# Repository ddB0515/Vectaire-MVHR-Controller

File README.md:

# Vectaire MVHR controller

<div align="center">
  
  <br><br>
  
  &nbsp;&nbsp;
  
</div>

ESP32 firmware that **replaces the original LCD control panel** of a Vectaire MVHR (heat-recovery ventilation) unit.
It is tested on the **Vectaire Midi** and may also work with the **Maxi**, which uses the same kind of panel (see
[MVHR units](#mvhr-units)).
The controller talks to the unit over its 12 V one-wire bus. It shows everything on its own touch screen, or works
without a screen, and you can also use it from a phone or a computer:

- **Local touch screen** (optional): home screen with temperatures, humidity, fan speed and alarms, plus menus for
  every setting the original panel had.
- **Web page** on your home network: live state, controls, settings, maintenance and diagnostics.
- **Home Assistant** through MQTT discovery. All sensors and controls appear by themselves.
- **Firmware updates over Wi-Fi**, with automatic rollback if a new version fails.

> The controller is the **only master** on the bus: it replaces the original panel, it doesn't sit next to it.
> Disconnect the original panel before you connect the controller.

---

## Contents

1. [Two variants](#two-variants)
2. [Supported hardware](#supported-hardware)
3. [Wiring to the MVHR](#wiring-to-the-mvhr)
4. [First start and Wi-Fi setup](#first-start-and-wi-fi-setup)
5. [Using the touch screen](#using-the-touch-screen)
6. [Web page](#web-page)
7. [Home Assistant](#home-assistant)
8. [Network time](#network-time)
9. [Fan speed settings](#fan-speed-settings)
10. [Not built yet](#not-built-yet)
11. [Device password](#device-password)
12. [Button and status LED](#button-and-status-led)
13. [Troubleshooting](#troubleshooting)
14. [Project layout](#project-layout)
15. [Building, flashing and updating: `idf.sh` and `ota.sh`](#building-flashing-and-updating-idfsh-and-otash)

---

## Two variants

The same code builds two variants:

| | **Display** | **Headless** |
|---|---|---|
| Board | NiceMCU C5E-DEV 2.8IPS (ESP32-C5, 2.8" touch screen) | Any ESP32, ESP32-C3, -S3, -C5 or -C6 board, 4 MB flash or more |
| Operated from | Touch screen, web page, Home Assistant | Web page, Home Assistant |
| Status shown on | Screen | A status LED (optional) |
| Wi-Fi | Optional ("Display only" mode works without it) | Required |
| Wi-Fi setup | Hotspot with a password and a QR code on the screen | Open hotspot that closes after 15 minutes |

Both variants have the same bus driver, web pages, Home Assistant integration and OTA updates.
An update can't install one variant's firmware on the other.

## Supported hardware

### Display variant

**NiceMCU C5E-DEV 2.8IPS**:
- ESP32-C5 (rev 1.2), 16 MB flash, 8 MB PSRAM,
- ST7789 320×240 IPS screen,
- CST816D touch controller.

The board's schematic, display spec and vendor demo are in [`docs/board/`](docs/board/).

### Headless variant

| Chip | Wi-Fi | Notes |
|---|---|---|
| ESP32 (classic, e.g. ESP32-D0WDQ6 DevKit) | 2.4 GHz | Wi-Fi setup and web page tested; not yet on a real bus |
| ESP32-S3 | 2.4 GHz | builds, not yet tested on hardware |
| ESP32-C3 | 2.4 GHz | builds, not yet tested on hardware |
| ESP32-C6 | 2.4 GHz | builds, not yet tested on hardware |
| ESP32-C5 | 2.4 + 5 GHz | builds, not yet tested on hardware |

PSRAM is not needed. The default pins for each chip are in [Wiring](#default-pins), and
[`docs/HEADLESS.md`](docs/HEADLESS.md) has more on the headless variant.

### MVHR units

| Unit | Status |
|---|---|
| **Vectaire Midi** | Tested: the controller runs in place of the original LCD panel |
| **Vectaire Maxi** | Not tested. It may work, as it uses the same LCD panel on the same one-wire bus, but check it carefully first |

The controller works with Vectaire units that use the original LCD panel on the one-wire bus (1200 baud). Units with
config block version 1.3 (49 bytes) and 2.0 (67 bytes) are recognised.

If you try it on a Maxi (or another Vectaire unit), keep the original panel so you can put it back, start with
**Diagnostics** to confirm the unit answers, and please report what works.

### Front panel (3D print)

[`midi-panel-3d-model/`](midi-panel-3d-model/) has a 3D-printable front panel for the display variant, made for the
**Vectaire Midi**:

| File | What it is |
|---|---|
| `Front Panel.stl` / `Front Panel.step` | The front panel that holds the display board |
| `PSU Plate.stl` / `PSU Plate.step` | The PSU plate |
| `Vectaire MVHR Screen Panel.f3d` | The Fusion 360 source, for changes |

Print the `.stl` files; the `.step` files are for other CAD programs. The photo at the top of this README shows the
panel fitted to a Midi.

You will also need **M3 threaded inserts** (heat-set into the printed parts):

| Part | Inserts |
|---|---|
| Front panel, for the screen | 4 × M3 × 4 mm |
| PSU plate | 4 × M3 × 5.5 mm |

## Wiring to the MVHR

The bus has a single signal wire that idles at **+12 V**, with the pull-up inside the unit. The controller needs two
GPIOs: one to **send** (TX), which pulls the bus low through an NPN transistor, and one to **receive** (RX), which reads
the bus through a voltage divider.

```
                     MVHR unit
              +12 V ───┐ (pull-up inside the unit)
                       │
   BUS ────────────────┴──────────┬───────────────────┐
                                  │                   │
                               C  │                 [15k]
   ESP TX ────[10k]────┬── B  NPN │ (e.g. 2N2222,     │
                       │       E  │  BC547)           ├──── ESP RX   (≈2.9 V at 12 V)
                     [100k]       │                   │
                       │          │                 [4.7k]
   GND ────────────────┴──────────┴───────────────────┴──── MVHR GND
```

- **TX:** the firmware inverts TX, so the transistor is off while the bus is idle. The 100k resistor from base to GND
  keeps the bus free while the ESP32 starts up.
- **RX:** the 15k/4.7k divider brings 12 V down to about 2.9 V. Don't use a divider that gives more than 3.3 V.
- **GND** of the controller and the unit must be connected.
- **Power:** use a proper supply. Some USB power banks switch off at low load, which restarts the controller.

Verified hardware adopter slightly modified is in `hardware` folder https://github.com/ddB0515/VectaireESP32/tree/main/hardware

### Default pins

| Board / chip | Bus TX | Bus RX | Button | Status LED |
|---|---|---|---|---|
| NiceMCU C5 (display) | IO2 (4-pin "I2C" connector, pin 3) | IO3 (pin 2) | GPIO28 | – |
| ESP32 | GPIO25 | GPIO26 | GPIO0 (BOOT) | GPIO2, single LED |
| ESP32-S3 | GPIO17 | GPIO18 | GPIO0 (BOOT) | GPIO48, WS2812 |
| ESP32-C3 | GPIO4 | GPIO5 | GPIO9 (BOOT) | GPIO8, WS2812 |
| ESP32-C6 | GPIO2 | GPIO3 | GPIO9 (BOOT) | GPIO8, WS2812 |
| ESP32-C5 (headless) | GPIO2 | GPIO3 | GPIO28 (BOOT) | GPIO27, WS2812 |

All pins can be changed. See [Changing pins and options](#changing-pins-and-options).

**Checking the wiring without a unit attached:** open the web page's **Diagnostics** and press **Run wiring test**.
It pulls the bus low for about 20 ms and checks that RX sees it.

## First start and Wi-Fi setup

### Display variant

On first start the screen offers two choices:

- **Wi-Fi & Home Assistant:** the controller opens a setup hotspot and shows a QR code.
  1. Scan the QR code with your phone to join the hotspot.
  2. The setup page opens by itself. Scan the second QR code if it doesn't.
  3. Pick your network, enter its password and, if you like, your MQTT broker.
- **Display only:** no Wi-Fi at all. Everything works from the touch screen.

### Headless variant

1. Power the controller up. With no Wi-Fi saved, it opens the **open hotspot** `Vectaire-XXXX`, and the LED blinks
   blue.
2. Join it with a phone. The setup page opens by itself, or go to `http://192.168.4.1/`.
3. **Write down the device password** shown at the top of the page.
4. Choose your Wi-Fi network, optionally enter your MQTT broker, and press **Connect**.

The hotspot closes after 15 minutes with nobody joined. Because it has no password, anyone nearby could join it while
it is up, so keep the setup short.

### After setup

The controller restarts and joins your network. From then on it is reachable at **`http://vectaire-xxxx.local/`**
(the name is on the setup page, and on the screen under Menu › Device). Use its IP address if your phone or computer
doesn't resolve `.local` names.

## Using the touch screen

**Home screen** shows:
- a house with the **airflow mode** under the roof (heat recovery in orange, bypass in blue, intake motor off in
  green, each with its icon) and the **inside temperature and humidity** along the bottom ("Low" below 35 %, "High"
  above 99 %, as on the original panel),
- the **intake and exhaust fan** percentages above the roof (intake left, exhaust right),
- the **outdoor temperature** on the right, with the current function below it when there is one (holiday, night
  mode …; "Boost active" during a boost),
- fan speed (1–3), with − and + buttons, and the bypass button,
- the time and date,
- a Wi-Fi icon (only while connected) and the Home Assistant logo (only while connected),
- an alarm banner when there is an alarm.

**Menu**:

| Item | What it does |
|---|---|
| Holiday | Off (normal ventilation) or On (reduced ventilation while away) |
| Night | Night mode (no boost during quiet hours): on/off, start and end time |
| Humidity | Humidity setpoint for automatic boost |
| Timers | Boost delay and overrun |
| Bypass | Summer bypass: auto, or forced on/off |
| Clock | Sets the unit's time and date by hand; **Network time** (see [Network time](#network-time)) |
| Filter | Filter saturation, hours of service, power outages; reset the filter counter after a filter change |
| Device | Wi-Fi, Home Assistant, dark theme, **dim after**, **dim level** (1, 5, 10, 25 or 50 %), **screen off after**, [**fan speeds**](#fan-speed-settings), **outdoor temp offset** (−10.0 to +10.0 °C in 0.1 steps), firmware version (tap it to see the device password) |

**Alarms** pop up by themselves. A **fire alarm** takes over the whole screen.

**Sleep:** the screen dims, then switches off when nobody touches it (both times and the dim level can be set under
Device). Tap to wake it: that first tap only wakes the screen and doesn't press anything. After 60 s without a touch it also goes back
to the home screen.

**Dark theme:** Menu › Device › Dark theme. It is saved and applied straight away.

## Web page

`http://vectaire-xxxx.local/` works on both variants and uses the phone's or computer's light or dark mode.

| Section | What's there |
|---|---|
| **Overview** | The same picture as the controller's home screen: airflow mode (with icon and colour), inside temperature and humidity, intake and exhaust fan %, outdoor temperature, and the current function |
| **Ventilation** | Fan speed, boost state (off / delay / on / overrun), bypass (with what it does now), holiday mode on/off |
| **Settings** | Humidity setpoint, boost delay, overrun, night mode, outdoor temperature offset |
| **Fan speed settings** | The installer fan percentages per speed. Shown only once the unit's settings have been read; editable when unlocked, see [Fan speed settings](#fan-speed-settings) |
| **Maintenance** | Filter saturation, reset filter counter, hours of service, the unit's clock (**Set unit clock to this device's time**, and [network time](#network-time)) |
| **Device** | Firmware, unit firmware, Wi-Fi, Home Assistant status, uptime; **Change Wi-Fi network** (scan, pick, password). The new network is tried first and kept only if it connects within 45 s, otherwise the controller goes back to the old one; **Change device password** (see [Device password](#device-password)) |
| **Changes** (at the bottom) | Unlock with the [device password](#device-password) to make changes; the password stays only in that browser tab |

Viewing needs no password; making changes does.

The links at the bottom open two more pages:
- **Home Assistant settings** (`/ha`): MQTT broker, user, password, the device name and how often readings are sent ("Update every", 5–3600 s, default 30; changes go out at once). Needs the device password; unlocking on the home page unlocks it too (same browser tab).
- **Diagnostics** (`/diag`): read-only, no password. Shows:
  - bus health and counters,
  - the last bus exchanges,
  - the wiring test,
  - the **unit's clock** as raw values (12/24 h, date format, time zone number, the UTC offset byte whose top bit may be the unit's own daylight saving flag),
  - the **outdoor temperature** three ways: as the unit reports it, the offset, and the value shown,
  - memory, Wi-Fi and the reason for the last restart,
  - a stored crash report, if there is one,
  - the full bus trace since start-up.

## Home Assistant

The controller uses **MQTT discovery**: once a broker is set, the device appears in Home Assistant with no YAML.
You need an MQTT broker (for example the Mosquitto add-on) and the MQTT integration.

1. Enter the broker during Wi-Fi setup, or later at `http://vectaire-xxxx.local/ha`.
2. Home Assistant shows a new device named after the controller (default "Vectaire MVHR").

| Type | Entities |
|---|---|
| Sensors | Inside/outside temperature, indoor humidity, intake/exhaust fan (%), mode (heat recovery / bypass / intake motor off), boost (off / delay / on / overrun), filter saturation, function, alarm, hours of service, power outages, Wi-Fi signal |
| Controls | Fan speed (1/2/3), bypass, holiday mode, night mode, humidity setpoint, boost delay, overrun |
| Binary sensors | Problem, fire alarm, frost protection |
| Button | Reset filter counter |

The **outdoor temperature** sent to Home Assistant includes the **outdoor temperature offset** (Menu › Device, or the
Settings card on the web page): a correction of −10.0 to +10.0 °C in 0.1 steps for a sensor that reads a little high or low.
The same corrected value is shown on the screen and the web page; the Diagnostics page lists the unit's own reading,
the offset and the shown value. The offset changes only what is displayed and reported, not what the unit itself uses.
A new offset reaches Home Assistant with the next regular update (the "Update every" time).

The entities show **unavailable** when the controller is offline, and also when the unit doesn't respond on the bus.

The **alarm** sensor reads "No alarm" when all is well (Home Assistant would show "Unknown" for the text "None").

MQTT topics, for the curious:
- discovery: `homeassistant/<component>/<id>/<obj>/config`
- state: `vectaire/<id>/state` (retained JSON)
- commands: `vectaire/<id>/<obj>/set`
- availability: `vectaire/<id>/status` and `vectaire/<id>/unit`

## Network time

The controller can set the unit's clock from the internet. It needs Wi-Fi, so it is **off by default**. The clock can
also always be set by hand: on the screen (Menu › Clock › Set time / Set date), or on the web page with **Set unit
clock to this device's time**, which uses the time of the phone or computer you are on.

| Setting | Meaning |
|---|---|
| **Network time** | On or off (Menu › Clock › Network time, or the web page's Maintenance card) |
| **Time zone** | Pick a city or region from the list, for example London, Berlin, New York / Toronto or Tokyo / Seoul. Each entry carries its standard (winter) time offset from UTC and its summer time rule. On the screen: Menu › Clock › Network time › Time zone (a scrolling list). On the web page: the Time zone menu, which shows entries as `(UTC+01:00) Berlin (summer time)` |

How it works:
- About a minute after start-up, and then **once a day**, the controller asks `pool.ntp.org` for the time.
- From that and the time zone it works out what the unit's clock should show, including the hour. The zone's summer
  time rule (last Sunday of March and October for the UK and Europe, second Sunday of March and first Sunday of
  November for the US and Canada) is used only to know whether summer time is on at that moment; the controller never
  moves the clock by itself on the changeover dates, so with network time off the clock only changes when you set it.
- If the clock is **more than 2 minutes out**, it is set to the right time (the unit has no seconds). If it is within
  2 minutes nothing is changed.
- With no Wi-Fi, no answer from the server or an unreadable clock, it tries again after about 10 minutes (5 minutes if
  the unit's clock could not be read). **Check now** (screen and web page) runs a check at once.
- The result of the last check is shown under the setting, for example "Last check 3 h ago: the clock was 5 min fast
  and was corrected."

The list holds regions whose summer time follows the European or the North American rule, plus regions with no summer
time (UTC, Reykjavik, Tokyo / Seoul, Dubai and others). Regions with southern-hemisphere summer time, such as Sydney
or Auckland, are not in the list. Without Wi-Fi the clock keeps running on the unit's own clock and is changed by hand
when needed.

To add a region, add a line to `components/mvhr_model/timezones.c`: the web page, the screen and the web preview all
read that one table.

> The night-mode quiet hours use the unit's clock, so a wrong time zone or rule moves them.

## Fan speed settings

The unit stores how hard each fan runs at speed 1, 2 and 3 (intake and exhaust separately, as set when the unit was
commissioned), plus a frost stall speed and a holiday reduction. The original panel hides these behind an installer
PIN. This firmware can show them, and change the six intake and exhaust values.

| Where | How |
|---|---|
| **Screen** | Menu › Device › **Fan speeds**. Tap a value, change it in whole percent (10–100), tap Set, read the warning, then Apply |
| **Web page** | **Fan speed settings** card. Unlock, edit the boxes (values show with a % sign; type just the number), press Save |

Both show a warning first. It says you are changing the fan speed balance and lists the **original values** so you can
write them down and put them back. The values are 10.0–100.0 % of full fan speed; the firmware refuses anything outside
that. Frost stall speed and holiday reduction are shown but cannot be changed.

How a change reaches the unit: the controller reads the unit's installer config block (49 bytes) again, changes only
the fan bytes you edited, writes the whole block back (command `0x10`), and reads it again to check. The log says
"now reports the new values" or "does NOT report the new values". All other installer settings are sent back exactly as
the unit gave them.

> **Be careful.** These settings change how much air each speed moves and the balance between intake and exhaust.
> Note the original values before changing anything, and change one value at a time while you check the unit.
> Changing the fan speeds has not yet been confirmed on every unit, so try it on one value first.

## Not built yet

- **Daylight saving without a network:** the controller does not change the clock by itself on the changeover dates.
  Network time (or setting it by hand) does that.
- **Southern-hemisphere summer time:** the time zone list has no Sydney, Auckland and similar regions, because only the
  European and North American summer time rules are built in.
- **More installer settings:** only the six intake and exhaust fan percentages can be changed. Frost stall speed and
  holiday reduction are shown but read-only, and the other installer settings (frost and bypass thresholds, heater
  threshold, handing) are not shown.
- **Fan speed write:** changing the fan speeds has not been confirmed on every unit.

## Device password

Each controller generates its own **device password** on its first start and keeps it in its flash. Updates don't
change it, but you can replace it with your own from the web page (see below). It protects:

- firmware updates over Wi-Fi,
- changes from the web page,
- the Home Assistant settings page,
- remote restart.

Where to find it:
- **Display:** Menu › Device, then tap the **Firmware** row.
- **Headless:** at the top of the setup page. Press the button for 1–4 s to open the setup hotspot again and read it.

The password is never stored on your computer by the tools in this project.

**Changing it:** on the home page, unlock with the current password, then **Device › Change device password**. The
first time, the current password is the generated one. Enter it again, then the new one twice: 8–32 characters,
letters, digits and symbols, no spaces. From then on the new password is needed for everything above (including
`tools/ota.sh`), and the screen (or the setup page, headless) shows the new one. The API is `POST /api/password` with
the current password in `X-OTA-Password` and `{"new":"..."}` as the body. A factory install over USB erases it and a
new one is generated.

## Button and status LED

| Button | Display | Headless |
|---|---|---|
| 1–4 s | – | Opens the setup hotspot (change Wi-Fi, see the device password); nothing is forgotten |
| Hold 5 s | Forgets Wi-Fi and restarts into the first-start choice | Forgets Wi-Fi and restarts into setup |

MQTT settings are kept in both cases.

**Status LED** (headless only; a WS2812 shows colours, a single LED shows only the blink pattern):

| State | Colour | Pattern |
|---|---|---|
| Fire alarm | red | fast flicker |
| Setup hotspot open | blue | blinks once a second |
| Unit not responding | red | double flash every 2 s |
| Connecting to Wi-Fi | yellow | short flash every 2 s |
| Other alarm (e.g. clean filters) | orange | on, short gap every 2 s |
| All fine | green | on |

## Troubleshooting

| Symptom | What to check |
|---|---|
| "Unit not responding" | Diagnostics › **Run wiring test**. **No bus voltage on RX:** check the BUS wire, the divider and GND. **TX doesn't pull the bus low:** check the transistor, the base resistor and the TX pin. |
| Unit responds only sometimes | Diagnostics › Bus: timeouts, CRC errors and bytes heard while idle. Make sure the original panel is disconnected. |
| Controller restarts by itself | Diagnostics › System › **Last restart**. "Power on" means the supply dropped (power banks do this); "Crash" comes with a stored crash report. |
| Can't reach `vectaire-xxxx.local` | On Linux, install `avahi-daemon` and `libnss-mdns`; under WSL, `ota.sh` asks Windows by itself. Or use the IP address (shown on the screen, in your router, or on the setup page after connecting). |
| Wrong Wi-Fi, or moved house | Still reachable: Device › Change Wi-Fi network on the web page. Otherwise hold the button for 5 s (or, headless, press it for 1–4 s) and run the setup again. Without Wi-Fi the controller restarts after 15 minutes offline, trying again. |
| Update didn't take | The new firmware rolls back by itself if it crashes or doesn't reach Wi-Fi within 5 minutes. Check the version under Device. |

## Project layout

| Path | What it is |
|---|---|
| `main/` | Start-up, button, Kconfig options (pins, LED, simulator) |
| `components/vectaire_bus` | Bus framing, CRC and UART transactions |
| `components/mvhr_model` | Polls the unit, decodes its data, sends commands; built-in **unit simulator** for development |
| `components/net` | Wi-Fi, setup hotspot and page, mDNS, OTA updates |
| `components/web` | Home page, diagnostics and JSON API |
| `components/ha` | Home Assistant (MQTT discovery) |
| `components/autoclock` | Daily network time for the unit's clock (summer time rules in `mvhr_model/dst.c`, the time zone list in `mvhr_model/timezones.c`, the decision logic in `mvhr_model/timesync.c`) |
| `components/settings` | Saved settings (NVS) |
| `components/status_led` | Headless status LED |
| `components/board`, `components/ui` | Display variant only: screen, touch, LVGL screens |
| `test/host/` | Unit tests for the bus codec, decoder and simulator; these run on a PC |
| `tools/` | `idf.sh`, `ota.sh`, `gen_icons.py` (screen icons), `web_preview.py` (web page preview) |
| `docs/` | [`HEADLESS.md`](docs/HEADLESS.md); `home_preview.html` (mock of the home screen); `board/`: vendor schematic, display spec and demo sketch |
| `midi-panel-3d-model/` | 3D-printable front panel and power supply plate for the Vectaire Midi (STL, STEP, Fusion 360) |
| `photos/` | Photos used in this README |

**Host tests** run on a PC and don't need ESP-IDF:

```bash
gcc -Icomponents/vectaire_bus/include -Icomponents/mvhr_model/include -Icomponents/mvhr_model -Itest/host/stub \
    components/vectaire_bus/vbus_codec.c components/mvhr_model/mvhr_decode.c test/host/test_decode.c \
    -o /tmp/test_decode && /tmp/test_decode
gcc -Icomponents/vectaire_bus/include -Icomponents/mvhr_model/include -Icomponents/mvhr_model -Itest/host/stub \
    components/vectaire_bus/vbus_codec.c components/mvhr_model/mvhr_decode.c components/mvhr_model/mvhr_sim.c \
    test/host/test_sim.c -o /tmp/test_sim && /tmp/test_sim
gcc -Icomponents/mvhr_model/include -Icomponents/mvhr_model -Itest/host/stub components/mvhr_model/dst.c \n    test/host/test_dst.c -o /tmp/test_dst && /tmp/test_dst
gcc -Icomponents/mvhr_model/include -Icomponents/mvhr_model -Itest/host/stub components/mvhr_model/dst.c     components/mvhr_model/timesync.c test/host/test_timesync.c -o /tmp/test_timesync && /tmp/test_timesync
```

**Unit simulator:** to develop without an MVHR, enable "Always use the built-in unit simulator" in menuconfig
(menu "Vectaire"). The bus UART is then not used at all. The simulated unit accepts the fan-speed config write too.

**Previewing the web page without building:** `python tools/web_preview.py [port]` serves
`components/web/www/home.html` straight from disk with made-up data, so you can edit the page and refresh the browser.
A "Preview controls" panel (bottom right) changes the data: function, airflow mode, temperatures, fan %, alarms,
Home Assistant and Wi-Fi status and so on. Any password unlocks the page. If the port is busy, pick another one;
old preview windows keep their port.

**Previewing the home screen:** open `docs/home_preview.html` in a browser. It is a mock of the controller's home
screen with switches for the Wi-Fi and Home Assistant icons and other states; it is not generated from the firmware, so
update it together with `components/ui/ui_home.c`.

**Icons:** the screen's icons are generated from SVG paths in `tools/gen_icons.py` into `components/ui/icons.c`
and `icons.h`. After changing icons run `python3 tools/gen_icons.py` (needs `librsvg2-bin` and `imagemagick`).

---

## Building, flashing and updating: `idf.sh` and `ota.sh`

### Setting up

The build tools are bash scripts and run on **Linux** or on **Windows 11 through WSL 2** (Windows Subsystem for Linux).
Both need **ESP-IDF v6.1**, installed with Espressif's installer (EIM) so that
`~/.espressif/tools/activate_idf_v6.1.sh` exists. `tools/idf.sh` uses that file; you never need to activate ESP-IDF
yourself. v5.5.4 still works (`tools/idf.sh --idf 5.5.4 build`, or `export VECTAIRE_IDF=5.5.4`).

The first build downloads the managed components (LVGL, mDNS, LED strip driver, and under v6 also MQTT and cJSON).

#### Linux (Ubuntu / Debian)

```bash
# build prerequisites, curl and python3 for ota.sh
sudo apt update
sudo apt install -y git wget flex bison gperf python3 python3-pip python3-venv cmake ninja-build ccache \
    libffi-dev libssl-dev dfu-util libusb-1.0-0 curl

# ESP-IDF Installation Manager (EIM) from Espressif's apt repository, then ESP-IDF v6.1
echo "deb [trusted=yes] https://dl.espressif.com/dl/eim/apt/ stable main" | sudo tee /etc/apt/sources.list.d/espressif.list
sudo apt update && sudo apt install -y eim
eim install -i v6.1

# access to USB serial ports (log out and back in afterwards)
sudo usermod -aG dialout $USER

# optional: open controllers by name (vectaire-xxxx.local)
sudo apt install -y avahi-daemon libnss-mdns
```

Then clone the project and build: `tools/idf.sh build`.

#### Windows 11 (WSL 2)

Everything runs inside an Ubuntu installation in WSL 2. The web pages open in your normal Windows browser.

1. **Install WSL with Ubuntu.** In PowerShell as administrator, run `wsl --install -d Ubuntu-24.04`, restart, and
   create your Linux user when Ubuntu starts.
2. **In the Ubuntu terminal,** run the same commands as for [Linux](#linux-ubuntu--debian) above. Skip avahi; Windows
   resolves `.local` names for `ota.sh`, see point 5.
3. **Clone the project inside WSL**, e.g. `cd ~ && git clone <repo-url>`. Not under `/mnt/c/...`: building there
   is many times slower. The repository's `.gitattributes` keeps the scripts' LF line endings even in a Windows
   checkout. A CRLF script fails with `bash\r: No such file or directory`; fix one with `git add --renormalize .`
   or a fresh clone.
4. **USB for flashing.** WSL doesn't see USB devices until Windows hands them over with
   [usbipd-win](https://github.com/dorssel/usbipd-win). In PowerShell:

   ```powershell
   winget install usbipd                     # once
   usbipd list                               # find the board: "USB-SERIAL CH340", "CP210x" or "USB JTAG/serial debug unit"
   usbipd bind --busid 1-4                   # once per board, as administrator (use your BUSID)
   usbipd attach --wsl --busid 1-4           # every time the board is plugged in
   ```

   In Ubuntu it then appears as `/dev/ttyUSB0` (CH340, CP210x) or `/dev/ttyACM0` (the chip's own USB). Check with
   `ls /dev/ttyUSB* /dev/ttyACM*`. If the port is missing, `tools/idf.sh` prints these steps. Opening the port
   resets some boards, the NiceMCU C5 among them; it may then drop off WSL, so run `usbipd attach` again.
5. **Over-the-air updates need no setup.** WSL 2 usually can't resolve `.local` names itself, so `tools/ota.sh` asks
   Windows for the address and prints it (`vectaire-xxxx.local is 192.168.1.50`). You can always pass the IP
   instead. If you use the controllers' names in other commands too (e.g. `curl`), turn on WSL's mirrored
   networking: add `[wsl2]` and `networkingMode=mirrored` to `%UserProfile%\.wslconfig`, then run `wsl --shutdown`.
6. **VS Code:** install the **WSL** extension, open the project folder from WSL (`code .` in the Ubuntu terminal), and
   install the ESP-IDF extension inside WSL. Point it at the same v6.1 (`~/.espressif/v6.1/esp-idf`); a build
   folder configured by another version is started over by `tools/idf.sh`.

After that, every command below is the same on Windows (in the Ubuntu terminal) and on Linux.

### `tools/idf.sh`: build and flash

`tools/idf.sh` runs ESP-IDF's `idf.py` with the pinned ESP-IDF version. You don't need an activated ESP-IDF shell, and
it works from scripts. Everything after the variant option goes straight to `idf.py`.

Each build folder remembers which ESP-IDF version configured it. If you switch versions (or VS Code's ESP-IDF
extension used another one in the same folder), `idf.sh` starts that folder over and keeps its `sdkconfig`.

```
tools/idf.sh [--idf <version>] [--headless <target>] <idf.py arguments>
```

| Variant | Build folder | Settings file | Firmware image |
|---|---|---|---|
| Display (default) | `build/` | `sdkconfig` | `build/vectaire_c5.bin` |
| `--headless esp32` | `build-headless-esp32/` | `build-headless-esp32/sdkconfig` | `build-headless-esp32/vectaire_headless.bin` |
| `--headless esp32c3` / `esp32s3` / `esp32c5` / `esp32c6` | `build-headless-<target>/` | inside that folder | `…/vectaire_headless.bin` |

The variants never share a build folder or settings file, so you can build all of them side by side.

**Display variant**, the NiceMCU C5 board:

```bash
tools/idf.sh build                              # build
tools/idf.sh -p /dev/ttyUSB0 flash              # flash over USB (first time, or to recover)
tools/idf.sh -p /dev/ttyUSB0 flash monitor      # flash and watch the log (Ctrl+] to quit)
tools/idf.sh menuconfig                         # settings, menu "Vectaire"
```

The board's USB serial chip is a CH340 (`/dev/ttyUSB0`, 115200 baud). Opening the serial port power-cycles this
board.

**Headless variant**, for example a classic ESP32:

```bash
tools/idf.sh --headless esp32 build
tools/idf.sh --headless esp32 -p /dev/ttyUSB0 flash
tools/idf.sh --headless esp32 -p /dev/ttyUSB0 monitor
tools/idf.sh --headless esp32 menuconfig
```

#### Changing pins and options

Run `menuconfig` for the variant and chip, open the **Vectaire** menu, save, then build again:

| Option | Meaning |
|---|---|
| MVHR bus TX GPIO | Output to the NPN base resistor |
| MVHR bus RX GPIO | Input from the 15k/4.7k divider |
| Button GPIO | Button to GND (5 s reset; headless 1–4 s setup) |
| Status LED | None, single LED on a GPIO, or WS2812 |
| Status LED GPIO / active low | LED pin; "active low" for LEDs wired to 3.3 V (e.g. ESP32-C3 Super Mini) |
| Always use the built-in unit simulator | Development without an MVHR |

The settings are kept per chip, in that build folder. Deleting the folder resets them to the defaults above.

### `tools/ota.sh`: update over Wi-Fi

Once a controller is on your network, you don't need USB any more. `tools/ota.sh` does the whole update:
1. builds the firmware,
2. uploads it to the controller,
3. waits until the controller is running the new version.

```
tools/ota.sh <host> [--no-build] [-p PASSWORD] [--headless <target>]
```

| Option | Meaning |
|---|---|
| `host` | Controller name or IP, e.g. `vectaire-xxxx.local`. Required, unless `$VECTAIRE_HOST` is set. A `.local` name WSL can't resolve is looked up through Windows |
| `--no-build` | Upload the image that is already built |
| `-p`, `--password` | The [device password](#device-password). Without it, `$VECTAIRE_OTA_PASSWORD` is used, or the script asks for it, hidden. Typing it at the prompt keeps it out of your shell history |
| `--headless <target>` | Build and upload the headless variant for that chip |

Examples:

```bash
# display board
tools/ota.sh vectaire-xxxx.local

# display board, already built, by IP
tools/ota.sh 192.168.1.50 --no-build

# headless ESP32
tools/ota.sh vectaire-xxxx.local --headless esp32
```

#### The device password

Every update needs the controller's **device password**. Each controller has its own, generated on its first start,
and updates don't change it. Find it on the controller:

- **Display:** Menu › Device, then tap the **Firmware** row.
- **Headless:** press the button (the BOOT button on most dev boards) for **1–4 s**, join the open hotspot
  `Vectaire-XXXX` with a phone, and read it at the top of the setup page. Don't hold the button for 5 s, which
  forgets the Wi-Fi settings. Leave the setup page without pressing Connect. The controller restarts into normal
  operation 15 minutes after nobody is joined, or right away if you press reset.

There are three ways to give the password to `ota.sh`, from most to least private:

| Way | Example | Notes |
|---|---|---|
| **Prompt** (recommended) | `tools/ota.sh vectaire-xxxx.local` | Asked for at the start, nothing shown while you type. Kept out of the shell history and the process list |
| **Environment variable** | `read -rs VECTAIRE_OTA_PASSWORD && export VECTAIRE_OTA_PASSWORD`<br>`tools/ota.sh vectaire-xxxx.local` | For several updates in one terminal session. `read -rs` keeps it out of the history; it is gone when the terminal closes |
| **`-p` option** | `tools/ota.sh vectaire-xxxx.local -p 'PASSWORD'` | Handy in scripts, but the password ends up in your shell history. Quote it |

Things to know:

- The password goes to the controller in a request header (`X-OTA-Password`). `ota.sh` hands it to `curl` through a
  pipe, so it doesn't show up in the process list either. It goes in plain text over your home network, like the web
  pages, so only update from a network you trust.
- **Nothing is stored on your computer.** Neither `ota.sh` nor anything else in this project saves the password.
- **Different controllers, different passwords.** For several controllers, give each one its own password (or
  `unset VECTAIRE_OTA_PASSWORD` between them).
- **Wrong password:** the controller answers after a 1 s delay, which slows down guessing. `ota.sh` stops with
  "upload refused: wrong password?" and where to find it. Nothing is installed.
- **Updates only over the home network.** While the setup hotspot is open, the controller refuses updates; finish or
  leave the setup first.
- **USB needs no password.** `tools/idf.sh [--headless <target>] -p /dev/ttyUSB0 flash` works without it and keeps the
  saved settings (Wi-Fi, MQTT, device password).

#### What happens during an update

1. The controller checks the password and that the image is Vectaire firmware **of the same variant**. A display
   image is refused by a headless controller, and the other way round. An image for another chip is refused too.
2. It writes the image to its spare slot and restarts into it.
3. The new firmware is **confirmed once it reconnects to Wi-Fi**. If it crashes, or doesn't reach Wi-Fi within
   5 minutes, the controller **rolls back** to the previous version by itself.
4. `ota.sh` waits up to 3 minutes for the new build time to show up and prints the result.

`ota.sh` prints numbered steps with the time since it started, so you can see where it is: `[1/6] Finding the
controller`, `[2/6] Device password`, `[3/6] Building` (the compiler's progress on one line; a failed build prints the
last 40 lines of its output), `[4/6] Checking the firmware image` (size and build time), `[5/6] Uploading` (a progress
bar on a terminal) and `[6/6] Waiting for the controller to restart`, with a line every 3 seconds saying whether it is
answering and which firmware it runs. With `--no-build` there are five steps.

A wrong password is answered after a 1 s delay, which slows down guessing. The script then tells you where to find
the password.

**Release habit:** raise `PROJECT_VER` in the top-level `CMakeLists.txt` for every release. The version shows on the
screen, on the web page and in Home Assistant.

### Releases (GitHub Actions)

[`.github/workflows/release.yml`](.github/workflows/release.yml) builds the two release variants in Espressif's
`espressif/idf:v6.1` Docker image, with the same `tools/idf.sh` commands as above:

| Variant | Board |
|---|---|
| `esp32c5-display` | NiceMCU C5E-DEV 2.8IPS (ESP32-C5 with touch screen) |
| `esp32-headless` | Classic ESP32 board without a screen |

The other headless chips (C3, S3, C5, C6) are built locally with `tools/idf.sh --headless <target> build`.

**Making a release:**

1. Raise `PROJECT_VER` in `CMakeLists.txt` (e.g. `0.9.1`) and commit.
2. Tag that commit with the same version (plain `x.y.z`, no `v` prefix) and push the tag:

   ```bash
   git tag 0.9.1
   git push origin 0.9.1
   ```

3. The workflow builds both variants and publishes a GitHub Release `0.9.1` with these files:

   | File | Use |
   |---|---|
   | `vectaire-<ver>-<variant>-ota.bin` | Update over Wi-Fi; keeps all settings |
   | `vectaire-<ver>-<variant>-factory.bin` | First install over USB at address 0 (`esptool.py --chip esp32c5 write_flash 0x0 <file>`, `--chip esp32` for headless). **Erases the saved settings**, the device password included |
   | `vectaire-<ver>-<variant>.elf` | Decoding a crash report from the Diagnostics page (`addr2line -e <file> <address>`) |
   | `SHA256SUMS` | Checksums |

A tag that doesn't match `PROJECT_VER` stops the workflow before anything is published. **Run workflow** on the
Actions tab builds the same files without a release; they stay attached to that run as artifacts.

To install a release's OTA file without building, send it as `ota.sh` would:

```bash
read -rsp 'Device password: ' p; echo
curl -fsS -H @<(printf 'X-OTA-Password: %s\n' "$p") \
     --data-binary @vectaire-0.9.1-esp32c5-display-ota.bin http://vectaire-xxxx.local/api/ota
unset p
```

The header comes from a pipe, so the password stays out of the process list and the shell history.

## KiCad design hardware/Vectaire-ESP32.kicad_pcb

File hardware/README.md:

This is verified and tested Adapter for Vectaire MVHR (Midi in my case)

# Left side

TOP
* Serial that will be connected to ESP32 display board (or headless board)
  
Bottom
* IN from MVHR that goues to XH 2.54 3pin connector (so each opening/disconnecting is easier)
* Jumper(Red) is if someone want to have external switch) needs to be bridged if want contact power/ON
  
RIGHT
* USB connector that convert 12V from MVHR to 5V for USB to power ESP32 boards/display

If anyone want to buy adapter or PCB have around 5 spare boards(assembled) and 10 clean PCB

Any support is appreciated

If you like what I'm doing please support me <br/>

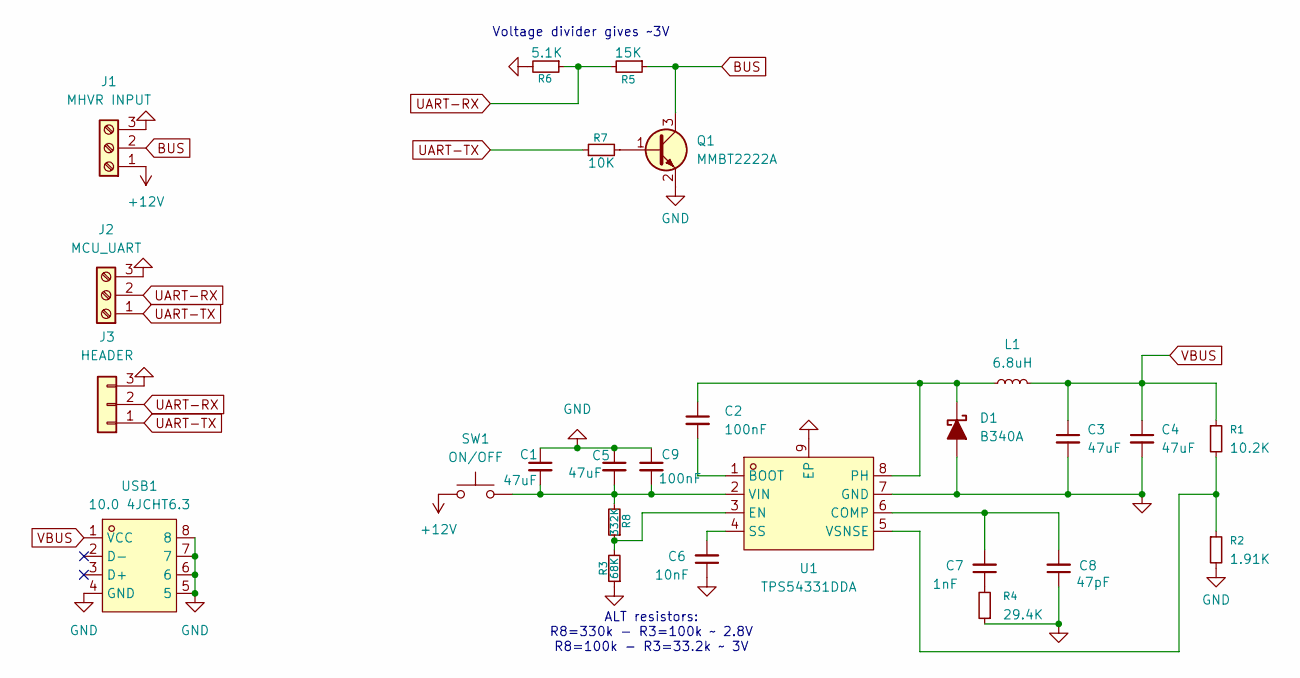
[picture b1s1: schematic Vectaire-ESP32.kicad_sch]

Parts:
C1, C3, C4, C5: 47uF; C_1206_3216Metric
C2, C9: 100nF; C_0603_1608Metric
C6: 10nF; C_0603_1608Metric
C7: 1nF; C_0603_1608Metric
C8: 47pF; C_0603_1608Metric
D1: B340A; D_SMA
J1: MHVR INPUT; TerminalBlock_TE_282834-3_1x03_P2.54mm_Horizontal
J2: MCU_UART; TerminalBlock_TE_282834-3_1x03_P2.54mm_Horizontal
J3: HEADER; PinHeader_1x03_P2.54mm_Vertical
L1: 6.8uH; L_Sunlord_MWSA0503S
Q1: MMBT2222A; SOT-23
R1: 10.2K; R_0603_1608Metric
R2: 1.91K; R_0603_1608Metric
R3: 68K; R_0603_1608Metric
R4: 29.4K; R_0603_1608Metric
R5: 15K; R_0603_1608Metric
R6: 5.1K; R_0603_1608Metric
R7: 10K; R_0603_1608Metric
R8: 332K; R_0603_1608Metric
SW1: ON/OFF; PinHeader_1x02_P2.54mm_Vertical
U1: TPS54331DDA; MPN TPS54331DDA; LCSC Part C1355528
USB1: 10.0 4JCHT6.3; SHOU HAN 10.0 4JCHT6.3; MPN 10.0 4JCHT6.3; LCSC Part C6331186

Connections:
+12V: J1.1, SW1.1
BUS: J1.2, Q1.3 (C), R5.1
GND: C1.1, C3.2, C4.2, C5.1, C6.1, C8.1, C9.1, D1.2 (A), J1.3, J2.3, J3.3, Q1.2 (E), R2.2, R3.1, R4.1, R6.2, U1.7 (GND), U1.9 (EP), USB1.4 (GND), USB1.5, USB1.6, USB1.7, USB1.8
unnamed: C7.1, R4.2
unnamed: C2.1, D1.1 (K), L1.1, U1.8 (PH)
unnamed: Q1.1 (B), R7.2
unnamed: C2.2, U1.1 (BOOT)
unnamed: C7.2, C8.2, U1.6 (COMP)
unnamed: R3.2, R8.1, U1.3 (EN)
unnamed: C6.2, U1.4 (SS)
unnamed: C1.2, C5.2, C9.2, R8.2, SW1.2, U1.2 (VIN)
unnamed: R1.2, R2.1, U1.5 (VSNSE)
UART-RX: J2.2, J3.2, R5.2, R6.1
UART-TX: J2.1, J3.1, R7.1
VBUS: C3.1, C4.1, L1.2, R1.1, USB1.1 (VCC)

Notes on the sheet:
Voltage divider gives ~3V
ALT resistors: R8=330k - R3=100k ~ 2.8V R8=100k - R3=33.2k ~ 3V

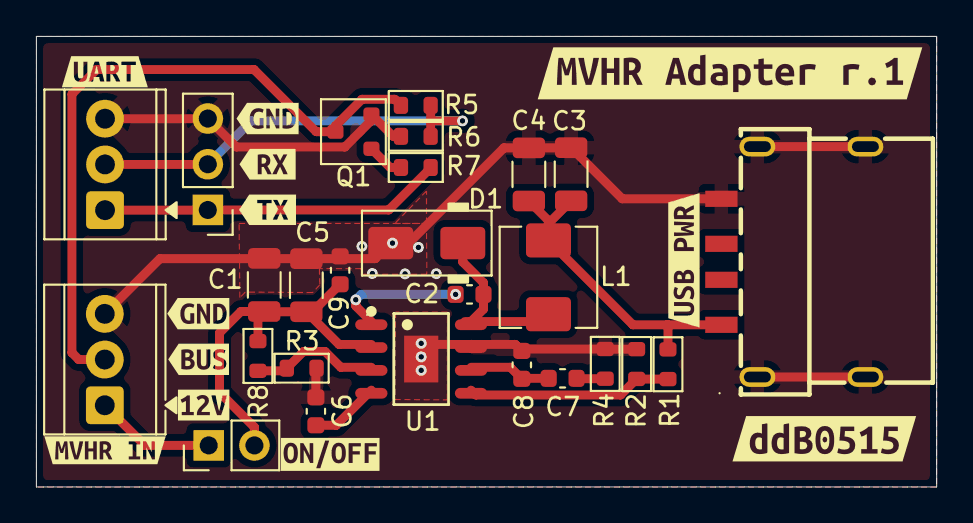
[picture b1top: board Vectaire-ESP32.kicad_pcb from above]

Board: 2 copper layers, 50.0 x 25.0 mm, 38 parts (0 on the bottom side), 15 nets.

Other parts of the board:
kibuzzard-6AE3E5AA: G***; kibuzzard-6AE3E5AA
kibuzzard-6AE3E51D: G***; kibuzzard-6AE3E51D
kibuzzard-6AE3E57C: G***; kibuzzard-6AE3E57C
kibuzzard-6AE3E59D: G***; kibuzzard-6AE3E59D
kibuzzard-6AE3E60B: G***; kibuzzard-6AE3E60B
kibuzzard-6AE3E511: G***; kibuzzard-6AE3E511
kibuzzard-6AE3E662: G***; kibuzzard-6AE3E662
kibuzzard-6AE3E678: G***; kibuzzard-6AE3E678
kibuzzard-6AE9CB1A: G***; kibuzzard-6AE9CB1A
kibuzzard-6AE48C81: G***; kibuzzard-6AE48C81
kibuzzard-6AE48CCB: G***; kibuzzard-6AE48CCB
kibuzzard-6AE48D3D: G***; kibuzzard-6AE48D3D
